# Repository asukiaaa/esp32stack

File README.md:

# ESP32Stack
A kicad project of stacking board with using ESP-WROOM-32.

In combination with [EmptyStack](https://github.com/asukiaaa/emptystack).

[schema](docs/esp32stack.pdf)

# Driver
This board uses CP2102 for serial communication.
For mac and windiws user, please install the following driver.
Linux supports cp2102 defaul, so linux user does not need any driver.

[CP210x USB to UART Bridge VCP Drivers](http://www.silabs.com/products/development-tools/software/usb-to-uart-bridge-vcp-drivers)

# Shop
[trial stacks](https://trialstacks.base.ec/items/6243777)

# Components
- [esp-wroop-32](http://akizukidenshi.com/catalog/g/gM-11647/)
- [Hirose-microB-USB](http://akizukidenshi.com/catalog/g/gC-05254/)
- [Diode](http://akizukidenshi.com/catalog/g/gI-05951/)
- [transistor MMBT3904](http://akizukidenshi.com/catalog/g/gI-05969/)
- [switch SKRPACE010](http://akizukidenshi.com/catalog/g/gP-06185/)
- [100uf 1206 condensor](http://akizukidenshi.com/catalog/g/gP-08260/)
- [10uf 0603 condensor](http://akizukidenshi.com/catalog/g/gP-07768/)
- [0.1uf 0603 condensor](http://akizukidenshi.com/catalog/g/gP-04940/)
- [1nf (1000pf) 0603 condensor](http://akizukidenshi.com/catalog/g/gP-09285/)
- [10k 0603 registor](http://akizukidenshi.com/catalog/g/gR-06103/)
- [led](http://akizukidenshi.com/catalog/g/gI-06417/)
- [CP2102](https://www.aliexpress.com/item/5pcs-Free-shipping-SILABS-CP2102-GMR-CP2102-QFN-28-offen-use-laptop-chip-100-new-original/32503317767.html?spm=2114.13010608.0.0.PUEIRm)
- [NCP1117ST33T3G](https://www.aliexpress.com/item/Free-Shipping-NCP1117ST33T3G-NCP1117-3-3V-linear-regulator-SOT-223-package/32244660148.html?spm=2114.13010608.0.0.PUEIRm)

# Footprints
- [ESP32-kiCAD-Footprints](https://github.com/adamjvr/ESP32-kiCAD-Footprints)
- [switch: SKRPACE010.kicad_mod](https://github.com/nosuz/kicad-lib/blob/master/module.pretty/SKRPACE010.kicad_mod)

# Programing software tools
ESP32Stack is a ESP-WROOM-32 breakout board so you can write your own program by usinig the following tools.

- [espressif/esp-idf](https://github.com/espressif/esp-idf)
- [espressif/arduino-esp32](https://github.com/espressif/arduino-esp32)
- [Mongoose OS](https://mongoose-os.com/)
- etc

# License
MIT

# References
- [ESP32-Core-Board-V2_sch.pdf](http://akizukidenshi.com/download/ds/espressifsystems/ESP32-Core-Board-V2_sch.pdf)
- [esp_wroom_32_datasheet_en.pdf](https://espressif.com/sites/default/files/documentation/esp_wroom_32_datasheet_en.pdf)
- [Enginursday: First Impressions of the ESP32](https://www.sparkfun.com/news/2017)
- [ESP32 Development Board with TELEC Memorial photograph](https://macsbug.wordpress.com/2016/12/12/esp32-development-board-with-telec-memorial-photograph/)
- [DS_FT232R](http://www.ftdichip.com/Support/Documents/DataSheets/ICs/DS_FT232R.pdf)
- [SparkFun FTDI Basic Breakout - 3.3V](https://www.sparkfun.com/products/9873)
- [Sehematic of SparkFun FTDI Basic Breakout - 3.3V](http://cdn.sparkfun.com/datasheets/BreakoutBoards/FTDI%20Basic-v22-3.3V.pdf)
- [esp32-thing.sch](https://cdn.sparkfun.com/assets/learn_tutorials/5/0/7/esp32-thing-schematic.pdf)
- [The Internet of Things with ESP32](http://esp32.net/)
- [ESP-WROVER-KIT_SCH-2.pdf](https://dl.espressif.com/dl/schematics/ESP-WROVER-KIT_SCH-2.pdf)
- [ESP32-EVB_Rev_A.pdf](https://github.com/OLIMEX/ESP32-EVB/blob/master/HARDWARE/REV-A/ESP32-EVB_Rev_A.pdf)

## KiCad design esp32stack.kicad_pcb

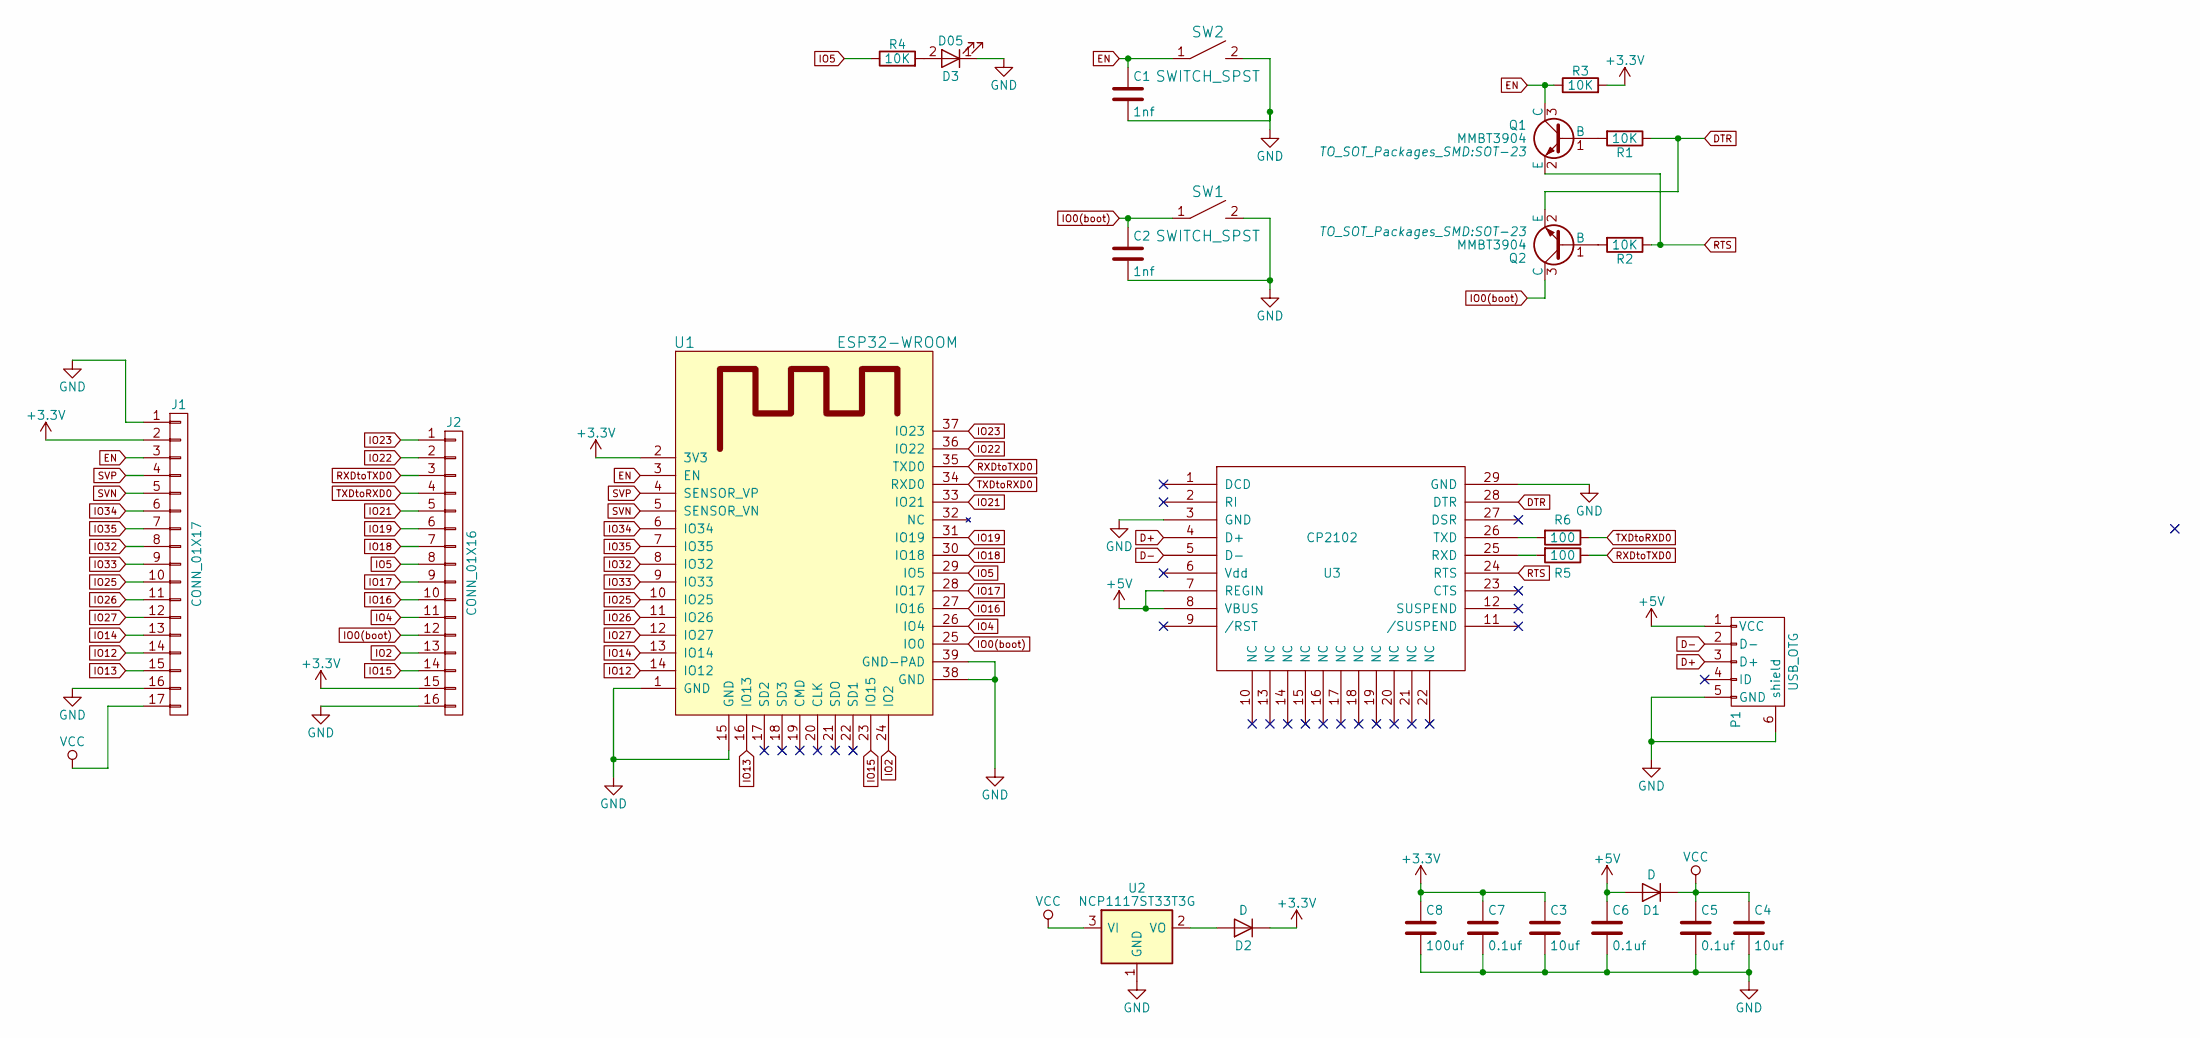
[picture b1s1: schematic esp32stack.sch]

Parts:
C1, C2: 1nf; C_0603
C3, C4: 10uf; C_0603
C5, C6, C7: 0.1uf; C_0603
C8: 100uf; C_1206
D1, D2: D; D_0805
D3: D05; LED_0603
J1: CONN_01X17; Pin_Header_Straight_1x17_Pitch2.54mm
J2: CONN_01X16; Pin_Header_Straight_1x16_Pitch2.54mm
P1: USB_OTG; USB_MICRO_B-HIROSE-ZX62R-B-5P
Q1, Q2: MMBT3904; SOT-23
R1, R2, R3, R4: 10K; R_0603
R5, R6: 100; R_0603
SW1, SW2: SWITCH_SPST; SKRPACE010
U1: ESP32-WROOM
U2: NCP1117ST33T3G; SOT-223
U3: CP2102; QFN-28-1EP_5x5mm_Pitch0.5mm

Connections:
+3V3: C3.1, C7.1, C8.1, D2.1 (K), J1.2, J2.15, R3.2, U1.2 (3V3)
+5V: C6.1, D1.2 (A), P1.1 (VCC), U3.7 (REGIN), U3.8 (VBUS)
D+: P1.3 (D+), U3.4 (D+)
D-: P1.2 (D-), U3.5 (D-)
DTR: Q2.2 (E), R1.1, U3.28 (DTR)
EN: C1.1, J1.3, Q1.3 (C), R3.1, SW2.1, U1.3 (EN)
GND: C1.2, C2.2, C3.2, C4.2, C5.2, C6.2, C7.2, C8.2, D3.1 (K), J1.1, J1.16, J2.16, P1.5 (GND), P1.6 (shield), SW1.2, SW2.2, U1.1 (GND), U1.15 (GND), U1.38 (GND), U1.39 (GND-PAD), U2.1 (GND), U3.3 (GND), U3.29 (GND)
IO0(boot): C2.1, J2.12, Q2.3 (C), SW1.1, U1.25 (IO0)
IO2: J2.13, U1.24 (IO2)
IO4: J2.11, U1.26 (IO4)
IO5: J2.8, R4.1, U1.29 (IO5)
IO12: J1.14, U1.14 (IO12)
IO13: J1.15, U1.16 (IO13)
IO14: J1.13, U1.13 (IO14)
IO15: J2.14, U1.23 (IO15)
IO16: J2.10, U1.27 (IO16)
IO17: J2.9, U1.28 (IO17)
IO18: J2.7, U1.30 (IO18)
IO19: J2.6, U1.31 (IO19)
IO21: J2.5, U1.33 (IO21)
IO22: J2.2, U1.36 (IO22)
IO23: J2.1, U1.37 (IO23)
IO25: J1.10, U1.10 (IO25)
IO26: J1.11, U1.11 (IO26)
IO27: J1.12, U1.12 (IO27)
IO32: J1.8, U1.8 (IO32)
IO33: J1.9, U1.9 (IO33)
IO34: J1.6, U1.6 (IO34)
IO35: J1.7, U1.7 (IO35)
unnamed: D2.2 (A), U2.2 (VO)
unnamed: D3.2 (A), R4.2
unnamed: Q1.1 (B), R1.2
unnamed: Q2.1 (B), R2.2
unnamed: R5.2, U3.25 (RXD)
unnamed: R6.2, U3.26 (TXD)
RTS: Q1.2 (E), R2.1, U3.24 (RTS)
RXDtoTXD0: J2.3, R5.1, U1.35 (TXD0)
SVN: J1.5, U1.5 (SENSOR_VN)
SVP: J1.4, U1.4 (SENSOR_VP)
TXDtoRXD0: J2.4, R6.1, U1.34 (RXD0)
VCC: C4.1, C5.1, D1.1 (K), J1.17, U2.3 (VI)

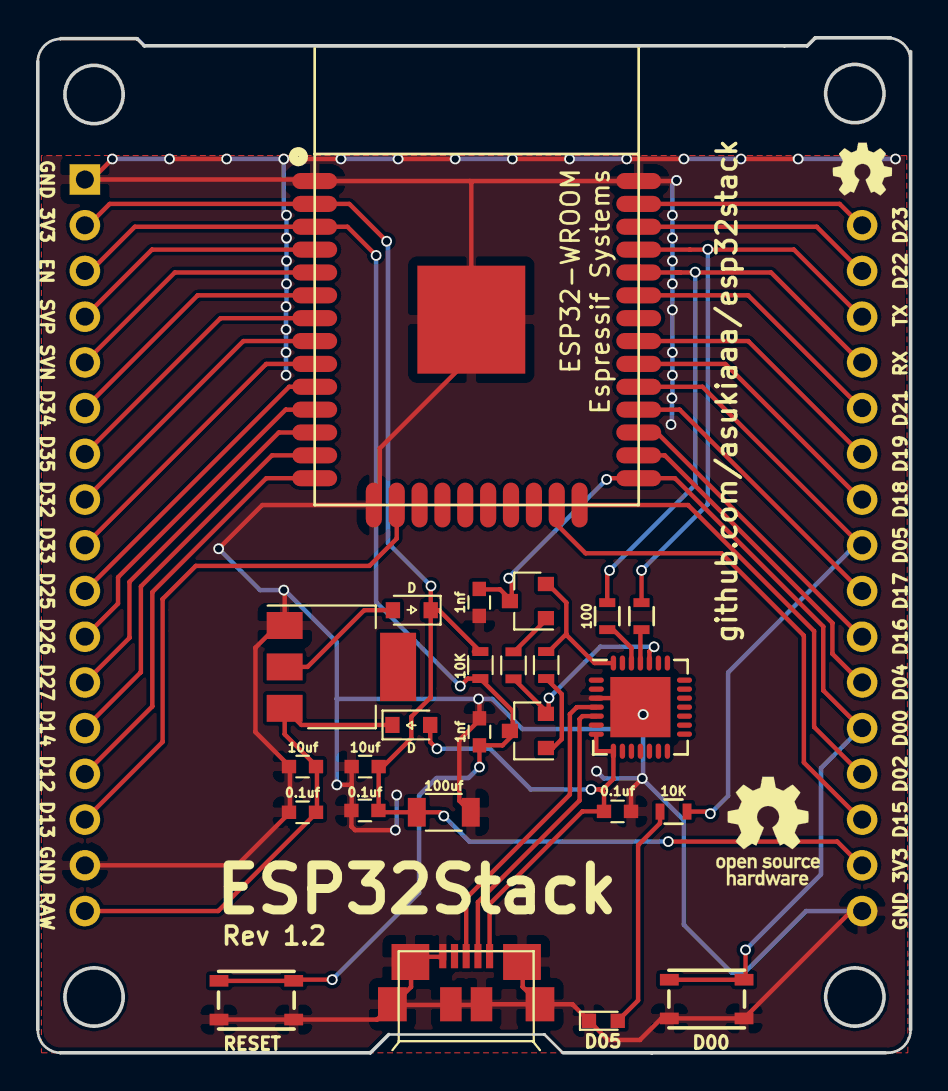
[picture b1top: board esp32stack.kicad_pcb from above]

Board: 2 copper layers, 48.5 x 56.4 mm, 27 parts (0 on the bottom side), 41 nets.

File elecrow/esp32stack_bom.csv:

Elecrow pn,Reference, Value, Footprint,url,memo
,P1,USB_OTG,usb_micro_b:USB_MICRO_B-HIROSE-ZX62R-B-5P,http://www.mouser.jp/ProductDetail/Hirose-Connector/ZX62R-B-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,
1023510A(10K),"R1,R2,R3,R4",10K,Resistors_SMD:R_0603,,
10240102A(100),"R5,R6",100,Resistors_SMD:R_0603,,
2011501A(1nf),"C1,C2",1nf,Capacitors_SMD:C_0603,,
2015010A(10uf),"C3,C4",10uf,Capacitors_SMD:C_0603,,
,"C5,C6,C7",0.1uf,Capacitors_SMD:C_0603,http://www.mouser.jp/ProductDetail/Yageo/CC0603JRNPO9BN101/?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,"There is no 0.1uf capacitor on list of Elecrow Parts Library.
If you have any stock of 0603 size 0.1nf capacitor, please use that."
,C8,100uf,Capacitors_SMD:C_1206,http://www.mouser.jp/ProductDetail/Taiyo-Yuden/JMK316ABJ107M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,
,"D1,D2",D,common:D_0805,http://www.mouser.jp/ProductDetail/ROHM-Semiconductor/RSX101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,
4040706A(green),D3,D05,LEDs:LED_0603,,
,J1,CONN_01X17,common:Pin_Header_Straight_1x17_Pitch2.54mm,"https://www.aliexpress.com/item/8-5-0-0-10-5mm-0-1-pitch-0-4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,searchweb201602_3_10152_10065_10151_10068_10136_10137_10060_10138_10155_10062_10156_10154_10056_10055_10054_10059_10099_10103_10102_10096_10148_10147_10052_10053_10142_10107_10050_10051_10084_10083_10080_10082_10081_10110_10175_10111_10112_10113_10114_10181_10037_10182_10032_10078_10079_10077_10073_10070_10123_10124,searchweb201603_16,ppcSwitch_7&btsid=46af219b-123f-4c85-aaf2-386de5b51161&algo_expid=12d844e6-d613-47bf-b44a-c32775f5904f-39&algo_pvid=12d844e6-d613-47bf-b44a-c32775f5904f","Footprint is pinheader(male) but expected component is pinsocket(female)
Cut the component to 17 pins or use similar one it has around 10mm length pin."
,J2,CONN_01X16,common:Pin_Header_Straight_1x16_Pitch2.54mm,"https://www.aliexpress.com/item/8-5-0-0-10-5mm-0-1-pitch-0-4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,searchweb201602_3_10152_10065_10151_10068_10136_10137_10060_10138_10155_10062_10156_10154_10056_10055_10054_10059_10099_10103_10102_10096_10148_10147_10052_10053_10142_10107_10050_10051_10084_10083_10080_10082_10081_10110_10175_10111_10112_10113_10114_10181_10037_10182_10032_10078_10079_10077_10073_10070_10123_10124,searchweb201603_16,ppcSwitch_7&btsid=46af219b-123f-4c85-aaf2-386de5b51161&algo_expid=12d844e6-d613-47bf-b44a-c32775f5904f-39&algo_pvid=12d844e6-d613-47bf-b44a-c32775f5904f","Footprint is pinheader(male) but expected component is pinsocket(female)
Cut the component to 16 pins or use similar one it has around 10mm length pin."
4020290A,"Q1,Q2",MMBT3904,TO_SOT_Packages_SMD:SOT-23,,
,"SW1,SW2",SWITCH_SPST,switch:SKRPACE010,http://www.mouser.jp/ProductDetail/ALPS/SKRPACE010/?qs=m0BA5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,
,U1,ESP32-WROOM,ESP32-footprints-Lib:ESP32-WROOM,http://akizukidenshi.com/catalog/g/gM-11850/,Please use modules that have telec mark.
,U2,NCP1117ST33T3G,TO_SOT_Packages_SMD:SOT-223,http://www.mouser.jp/ProductDetail/ON-Semiconductor/NCP1117S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,
,U3,CP2102,Housings_DFN_QFN:QFN-28-1EP_5x5mm_Pitch0.5mm,http://www.mouser.jp/ProductDetail/Silicon-Labs/CP2102N-A01-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,

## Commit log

2017-04-20 Initial commit for esp32stack rev1.0
2017-04-20 Add name silk to back side
2017-04-22 Adjust hole position
2017-04-22 Create schema pdf
2017-04-26 Add length
2017-04-27 Add silk
2017-04-28 Change condensor position
2017-04-29 Add images
2017-04-30 Change pcb layout for rev1.1
2017-04-30 Rename bom file name
2017-04-30 Change usb connector and led position for rev1.2
2017-04-30 Add requirements for elecrow pcba order
2017-05-03 Add shop info
2017-05-28 Add driver info
2017-06-13 Show hole size and position
